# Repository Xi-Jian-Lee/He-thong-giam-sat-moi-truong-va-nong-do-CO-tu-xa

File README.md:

Tên đề tài: Nghiên cứu, thiết kế và phát triển hệ thống IoT giám sát môi trường và nồng độ CO từ xa dựa trên cảm biến nhiệt độ, khói và lửa.

Sơ lược đề tài: ESP32 thu thập dữ liệu từ cảm biến khói, lửa và nhiệt độ. ESP32 sẽ xử lý dữ liệu để hiện ra màn hình OLED và đồng thời gửi về giao diện người dùng, sử dụng ứng dụng Blynk IoT. Bên cạnh đó, ESP32 sẽ kích hoạt còi hoặc loa để cảnh báo các trường hợp đặc biệt.

Video giới thiệu vận hành sản phẩm: https://youtu.be/24HGrBEQO44

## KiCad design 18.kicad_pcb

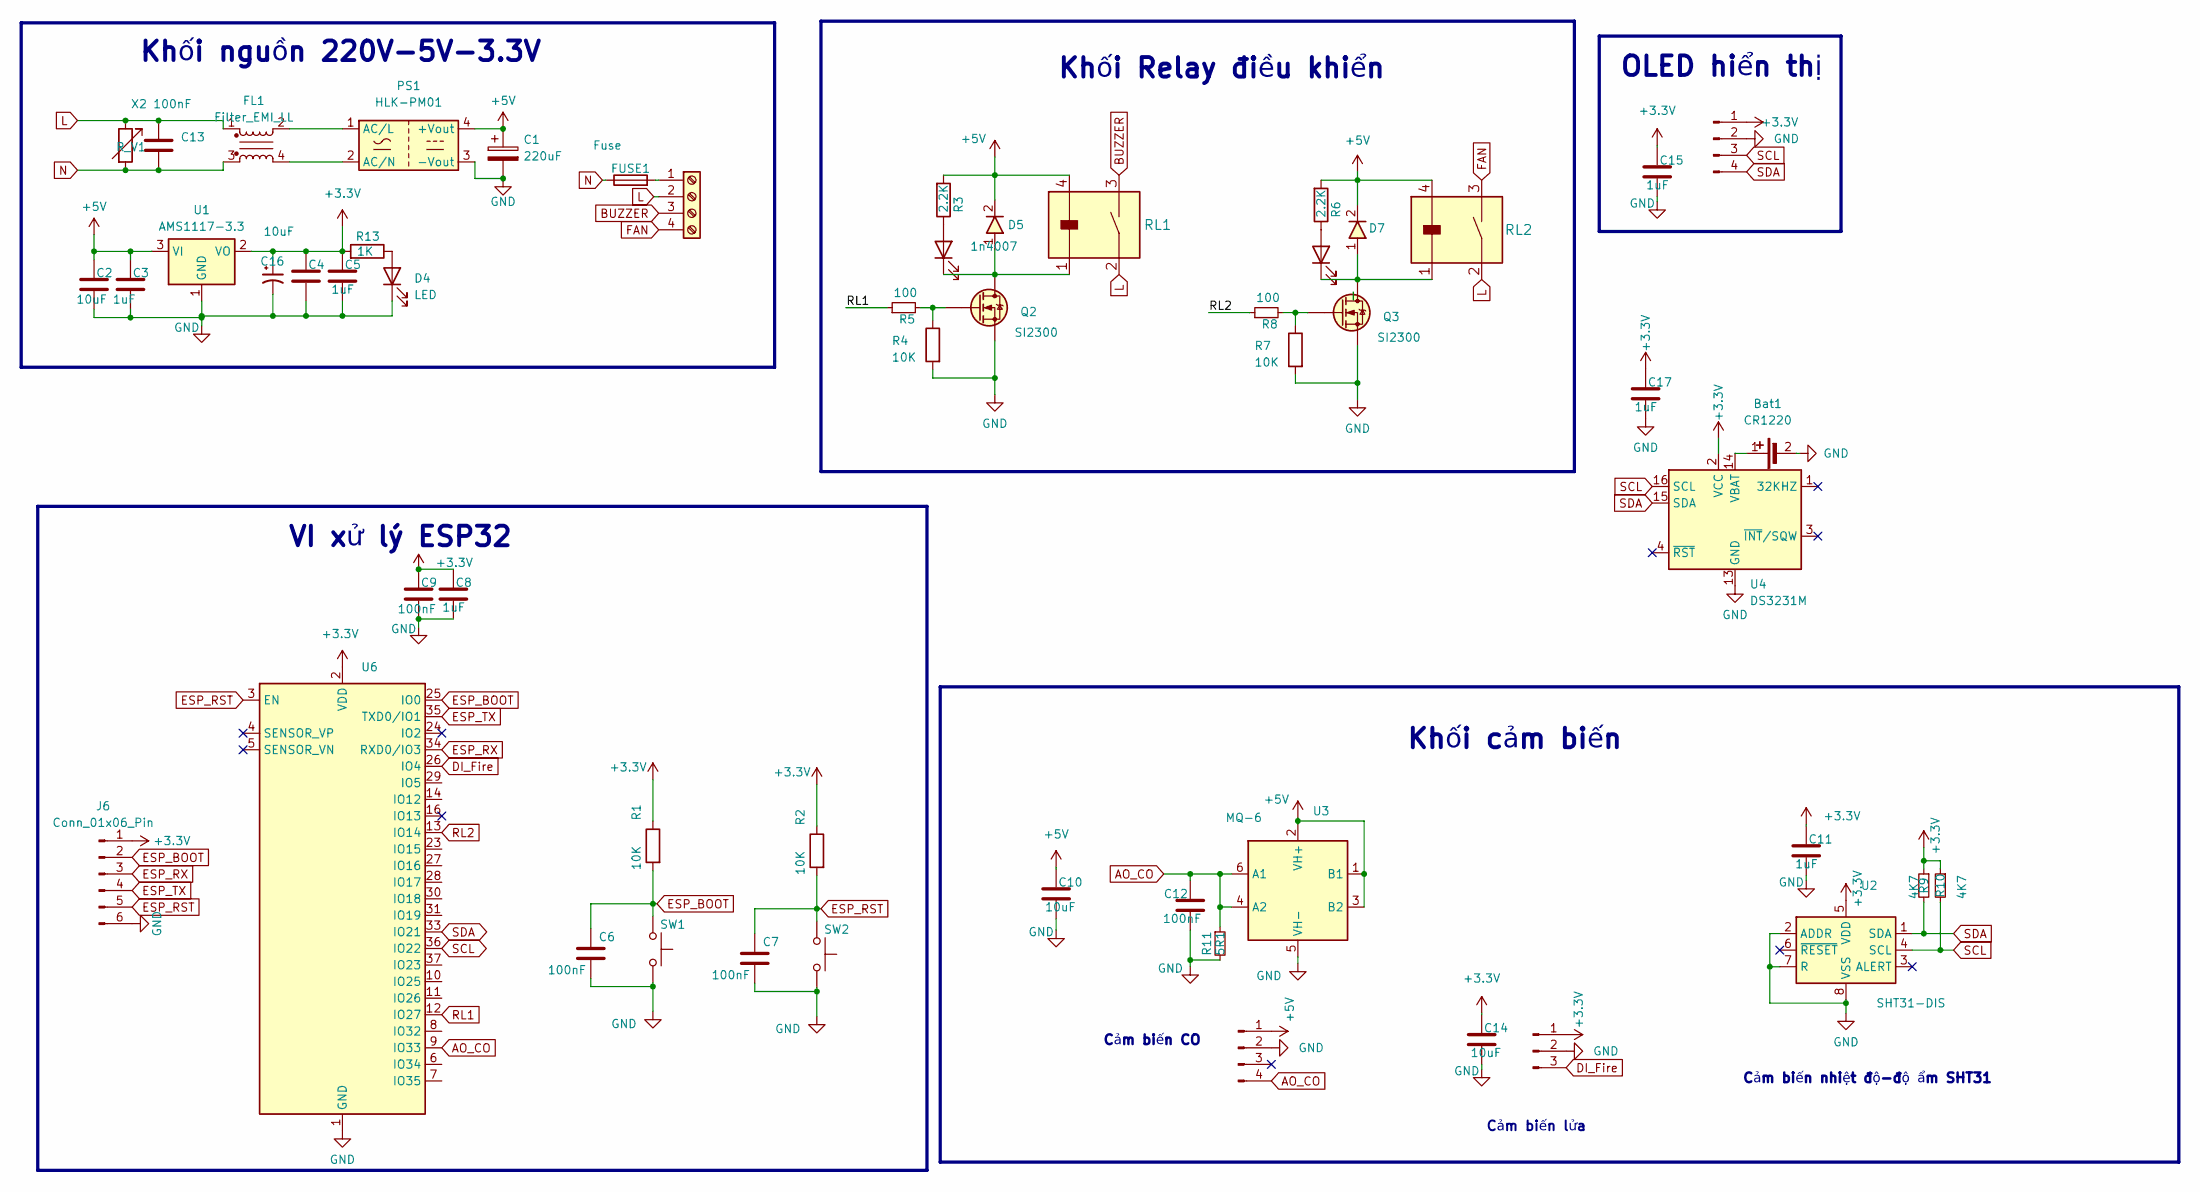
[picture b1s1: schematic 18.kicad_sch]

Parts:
Bat1: CR1220; BatteryHolder_CR1220
C1: 220uF; CP_Elec_8x10.5
C2, C4, C10, C14: 10uF; C_0603
C3, C5, C8, C11, C15, C17: 1uF; C_0603
C6, C7, C9, C12: 100nF; C_0603
C13: X2 100nF; C_Rect_L16.5mm_W6.0mm_P15.00mm_MKT
C16: C_Polarized_Small_US; Tantalum_1206
D1, D2: LED; LED_0603
D4: LED; LED_0603_1608Metric
D5, D7: 1n4007; D_SOD-123
FL1: Filter_EMI_LL; ACFilterChokeUU9.8
FUSE1: Fuse; Fuse_Bourns_MF-RG300
J1, J4: Conn_01x04_Pin; PinHeader_1x04_P2.54mm_Vertical
J2: Conn_01x03_Pin; PinHeader_1x03_P2.54mm_Vertical
J3: Screw_Terminal_01x04; TerminalBlock_Screw_HB9500_4P_P9.5mm
J6: Conn_01x06_Pin; PinHeader_1x06_P2.54mm_Vertical
PS1: HLK-PM01; Converter_ACDC_Hi-Link_HLK-PMxx
Q2, Q3: SI2300; SOT23-3
R1, R2, R4, R7: 10K; R_0603
R3, R6: 2.2K; R_0603
R5, R8: 100; R_0603
R9, R10: 4K7; R_0603
R11: 5R1; R_0603
R13: 1K; R_0603
RL1, RL2: Relay_G5NB-1A-E_DC5; Relay_G5NB-1A-E DC5
R_V1: 10D751K; RV_Disc_D12mm_W5.8mm_P7.5mm
SW1, SW2: SW_Push; SW_SPST_CK_RS282G05A3
U1: AMS1117-3.3; SOT-223-3_TabPin2
U2: SHT31-DIS; Sensirion_DFN-8-1EP_2.5x2.5mm_P0.5mm_EP1.1x1.7mm
U3: MQ-6
U4: DS3231M; SOIC-16W_7.5x10.3mm_P1.27mm
U6: ESP32-WROOM-32E

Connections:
+3.3V: C4.1, C5.1, C8.1, C9.1, C11.1, C14.1, C15.1, C16.1, C17.1, J2.1, J4.1, J6.1, R1.1, R2.1, R9.1, R10.1, R13.2, U1.2 (VO), U2.5 (VDD), U4.2 (VCC), U6.2 (VDD)
+5V: C1.1, C2.1, C3.1, C10.1, D5.2, D7.2, J1.1, PS1.4 (+Vout), R3.2, R6.2, RL1.4, RL2.4, U1.3 (VI), U3.1 (B1), U3.2 (VH+), U3.3 (B2)
AO_CO: C12.1, J1.4, R11.1, U3.4 (A2), U3.6 (A1), U6.9 (IO33)
BUZZER: J3.3, RL1.3
DI_Fire: J2.3, U6.26 (IO4)
ESP_BOOT: C6.1, J6.2, R1.2, SW1.2, U6.25 (IO0)
ESP_RST: C7.1, J6.5, R2.2, SW2.2, U6.3 (EN)
ESP_RX: J6.3, U6.34 (RXD0/IO3)
ESP_TX: J6.4, U6.35 (TXD0/IO1)
FAN: J3.4, RL2.3
GND: Bat1.2 (-), C1.2, C2.2, C3.2, C4.2, C5.2, C6.2, C7.2, C8.2, C9.2, C10.2, C11.2, C12.2, C14.2, C15.2, C16.2, C17.2, D4.2 (K), J1.2, J2.2, J4.2, J6.6, PS1.3 (-Vout), Q2.2 (S), Q3.2 (S), R4.2, R7.2, R11.2, SW1.1, SW2.1, U1.1 (GND), U2.2 (ADDR), U2.7 (R), U2.8 (VSS), U2.9 (VSS), U3.5 (VH-), U4.5 (GND), U4.6 (GND), U4.7 (GND), U4.8 (GND), U4.9 (GND), U4.10 (GND), U4.11 (GND), U4.12 (GND), U4.13 (GND), U6.1 (GND), U6.15 (GND), U6.38 (GND), U6.39 (GND)
L: C13.1, FL1.1, J3.2, RL1.2, RL2.2, R_V1.1
N: C13.2, FL1.3, FUSE1.1, R_V1.2
unnamed: Bat1.1 (+), U4.14 (VBAT)
unnamed: D1.1 (A), R3.1
unnamed: D1.2 (K), D5.1, Q2.3 (D), RL1.1
unnamed: D2.1 (A), R6.1
unnamed: D2.2 (K), D7.1, Q3.3 (D), RL2.1
unnamed: D4.1 (A), R13.1
unnamed: FUSE1.2, J3.1
unnamed: FL1.2, PS1.1 (AC/L)
unnamed: FL1.4, PS1.2 (AC/N)
unnamed: Q2.1 (G), R4.1, R5.2
unnamed: Q3.1 (G), R7.1, R8.2
RL1: R5.1, U6.12 (IO27)
RL2: R8.1, U6.13 (IO14)
SCL: J4.3, R10.2, U2.4 (SCL), U4.16 (SCL), U6.36 (IO22)
SDA: J4.4, R9.2, U2.1 (SDA), U4.15 (SDA), U6.33 (IO21)

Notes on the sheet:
Khối cảm biến
OLED hiển thị
VI xử lý ESP32
Cảm biến nhiệt độ-độ ẩm SHT31
Khối Relay điều khiển
Khối nguồn 220V-5V-3.3V
Cảm biến CO
Cảm biến lửa

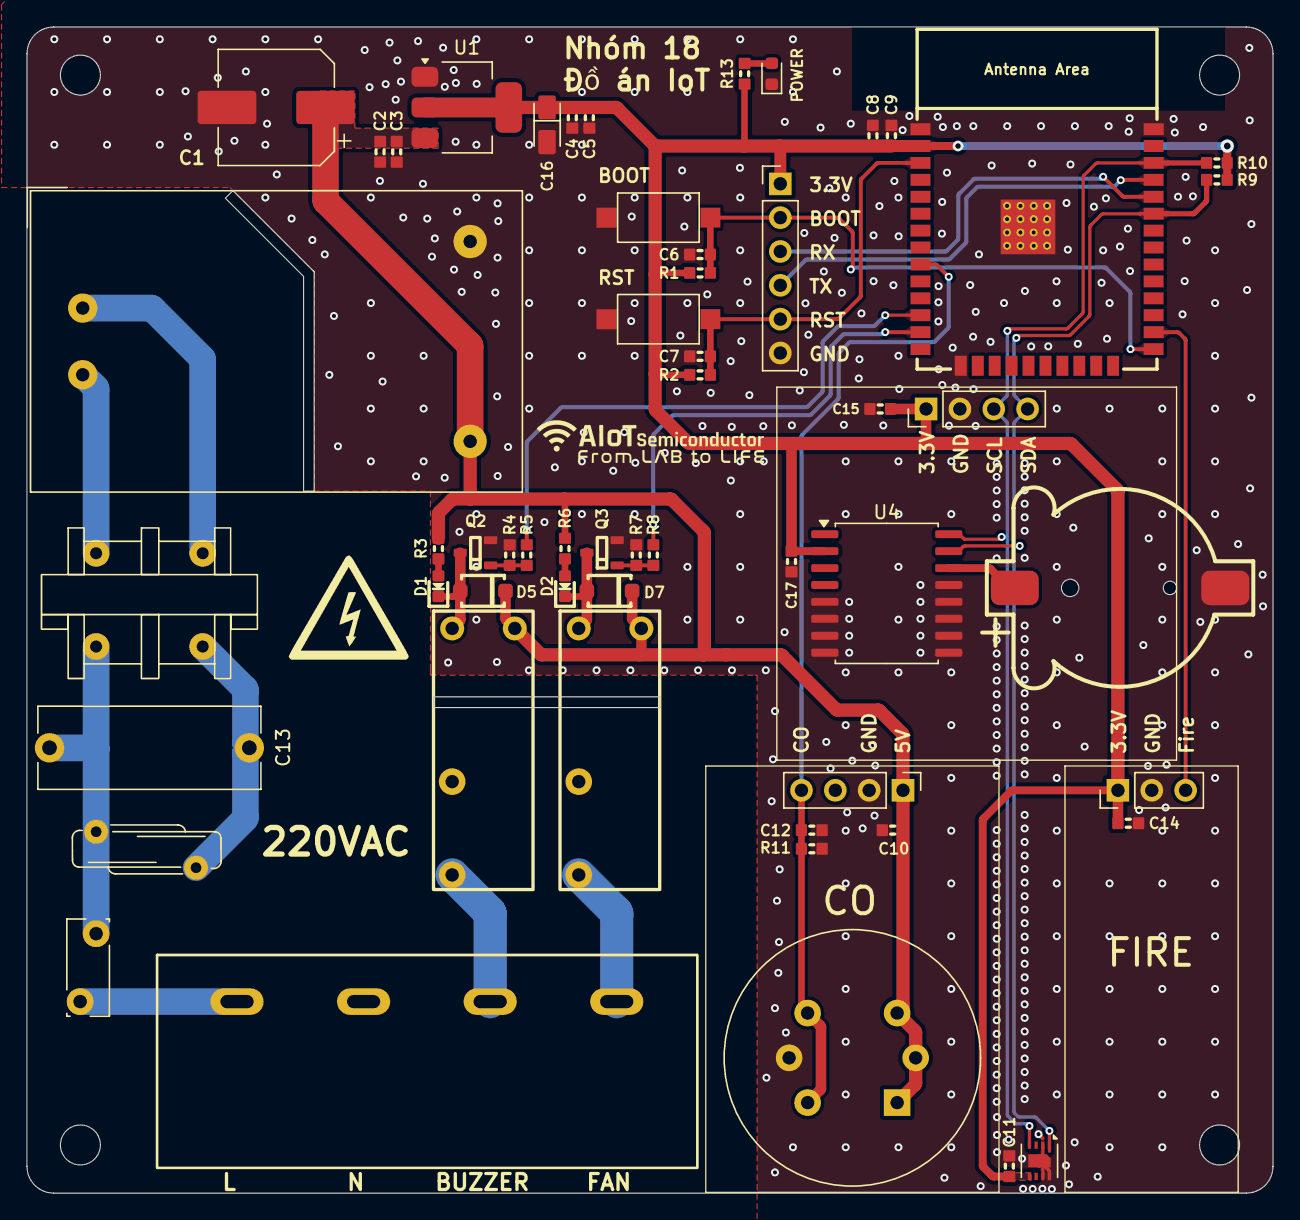
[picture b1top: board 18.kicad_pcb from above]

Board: 2 copper layers, 93.5 x 87.5 mm, 55 parts (0 on the bottom side), 28 nets.

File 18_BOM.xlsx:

STT | Tên | Giá trị | Footprint
1 | C3 | 1uF | C_0603
2 | C5 | 1uF | C_0603
3 | C8 | 1uF | C_0603
4 | C11 | 1uF | C_0603
5 | C15 | 1uF | C_0603
6 | C17 | 1uF | C_0603
7 | C2 | 10uF | C_0603
8 | C4 | 10uF | C_0603
9 | C10 | 10uF | C_0603
10 | C14 | 10uF | C_0603
11 | C6 | 100nF | C_0603
12 | C7 | 100nF | C_0603
13 | C9 | 100nF | C_0603
14 | C12 | 100nF | C_0603
15 | C1 | 220uF | CP_Elec_8x10.5
16 | C13 | X2 100nF | C_Rect_L16.5mm_W6.0mm_P15.00mm_MKT
17 | C16 | C_Polarized_Small_US | Tantalum_1206
18 | R1 | 10K | R_0603
19 | R2 | 10K | R_0603
20 | R4 | 10K | R_0603
21 | R7 | 10K | R_0603
22 | R3 | 2.2K | R_0603
23 | R6 | 2.2K | R_0603
24 | R5 | 100 | R_0603
25 | R8 | 100 | R_0603
26 | R9 | 4K7 | R_0603
27 | R10 | 4K7 | R_0603
28 | R11 | 5R1 | R_0603
29 | R13 | 1K | R_0603
30 | D1 | LED | LED_0603
31 | D2 | LED | LED_0603
32 | D5 | 1n4007 | D_SOD-123
33 | D7 | 1n4007 | D_SOD-123
34 | D4 | LED | LED_0603_1608Metric
35 | U1 | AMS1117-3.3 | SOT-223-3_TabPin2
36 | U2 | SHT31-DIS | Sensirion_DFN-8-1EP_2.5x2.5mm_P0.5mm_EP1.1x1.7mm
37 | U3 | MQ-6 | MQ-6
38 | U4 | DS3231M | SOIC-16W_7.5x10.3mm_P1.27mm
39 | U6 | ESP32-WROOM-32E | ESP32-WROOM-32E
40 | SW1 | SW_Push | SW_SPST_CK_RS282G05A3
41 | SW2 | SW_Push | SW_SPST_CK_RS282G05A3
42 | Q2 | SI2300 | SOT23-3
43 | Q3 | SI2300 | SOT23-3
44 | RL1 | Relay_G5NB-1A-E_DC5 | Relay_G5NB-1A-E DC5
45 | RL2 | Relay_G5NB-1A-E_DC5 | Relay_G5NB-1A-E DC5
46 | Bat1 | CR1220 | BatteryHolder_CR1220
47 | FL1 | Filter_EMI_LL | ACFilterChokeUU9.8
48 | FUSE1 | Fuse | Fuse_Bourns_MF-RG300
49 | PS1 | HLK-PM01 | Converter_ACDC_Hi-Link_HLK-PMxx
50 | R_V1 | 10D751K | RV_Disc_D12mm_W5.8mm_P7.5mm
51 | J1 | Conn_01x04_Pin | PinHeader_1x04_P2.54mm_Vertical
52 | J4 | Conn_01x04_Pin | PinHeader_1x04_P2.54mm_Vertical
53 | J2 | Conn_01x03_Pin | PinHeader_1x03_P2.54mm_Vertical
54 | J3 | Screw_Terminal_01x04 | TerminalBlock_Screw_HB9500_4P_P9.5mm
55 | J6 | Conn_01x06_Pin | PinHeader_1x06_P2.54mm_Vertical

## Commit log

2026-05-01 Mạch hệ thống
2026-05-01 Code chương trình
2026-05-01 Giới thiệu.md

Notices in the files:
parts and their libraries:
Copyright 2021 Accelerated Designs. All rights reserved.
